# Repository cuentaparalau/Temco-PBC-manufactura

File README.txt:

-----------TEMCO Grupo 9-----------
Juan Arzola
Alexis Rabiller
Manuel Simon
-----------------------------------

Para los part number se usaron los entregados por los fabricantes
Se verifico la disponibilidad de las componentes con su respectivo part-number en DigiKey
En el .zip se encuentran los archivos de manufactura

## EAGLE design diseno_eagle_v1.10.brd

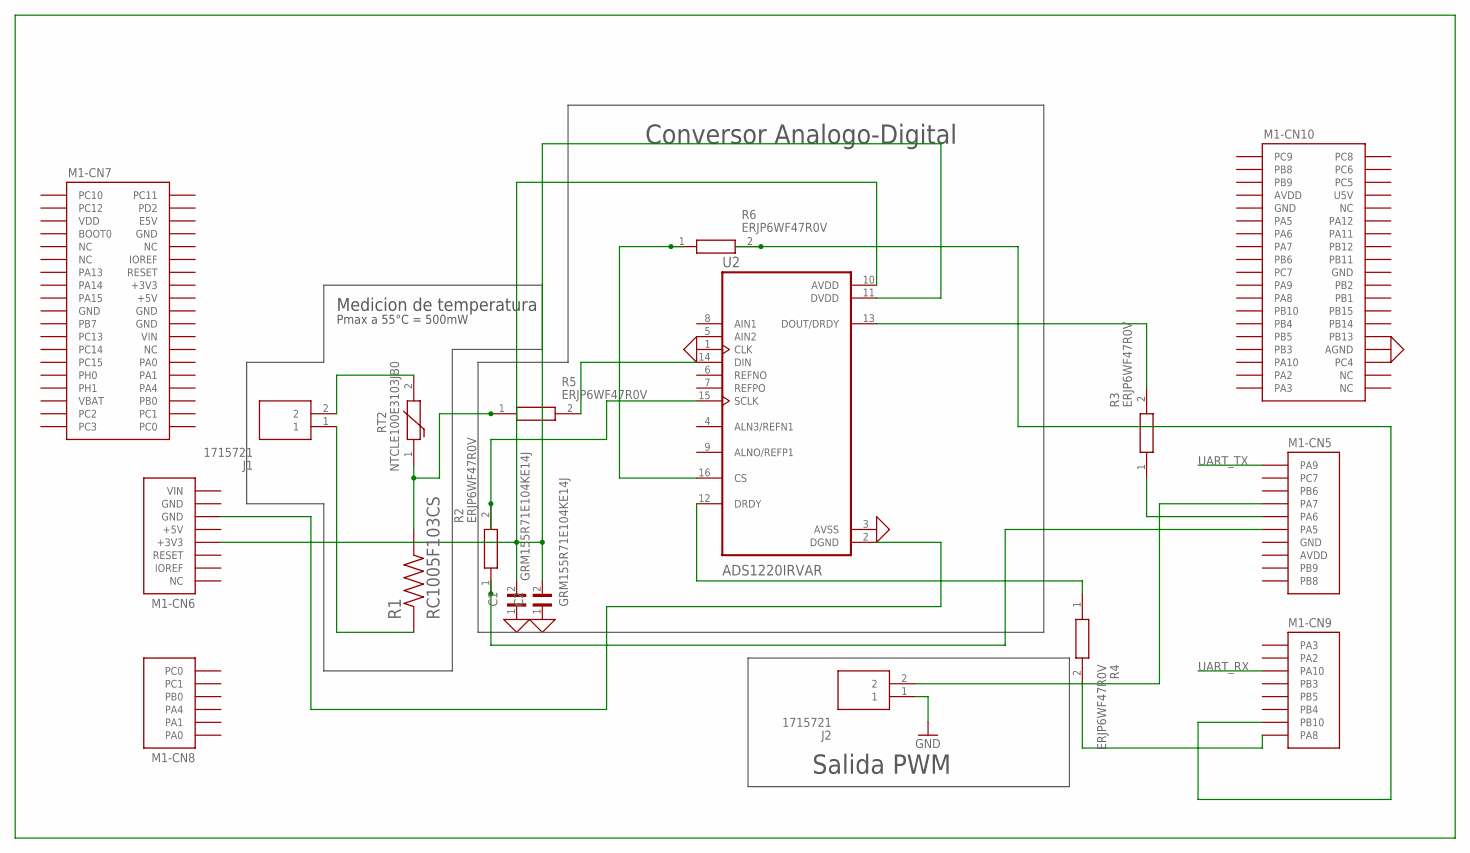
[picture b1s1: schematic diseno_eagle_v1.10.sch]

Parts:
C1, C2: GRM155R71E104KE14J; CAPC1005X55N
J1, J2: 1715721
M1: NUCLEO-L452RE; NUCLEO-64
R1: RC1005F103CS; RESC1005X40N
R2, R3, R4, R5, R6: ERJP6WF47R0V; RESC2012X75N
RT2: NTCLE100E3103JB0
U2: ADS1220IRVAR; QFN50P350X350X100-17N

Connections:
0: C1.1, C2.1, M1.CN10-32 (AGND), U2.1 (CLK), U2.3 (AVSS)
+3V3: M1.CN7-16 (+3V3)
+5V: M1.CN6-5 (+5V), M1.CN7-18 (+5V)
AVDD: M1.CN5-8 (AVDD), M1.CN10-7 (AVDD)
GND: J2.1, M1.CN5-7 (GND), M1.CN6-7 (GND), M1.CN7-8 (GND), M1.CN7-19 (GND), M1.CN7-20 (GND), M1.CN7-22 (GND), M1.CN10-9 (GND), M1.CN10-20 (GND)
IOREF: M1.CN6-2 (IOREF)
unnamed: R4.1, U2.12 (DRDY)
unnamed: R3.2, U2.13 (DOUT/DRDY)
unnamed: R1.2, R5.1, RT2.1
unnamed: M1.CN5-6 (PA5), R2.1
unnamed: M1.CN9-7 (PB10), R6.2
unnamed: M1.CN5-5 (PA6), R3.1
unnamed: C1.2, C2.2, M1.CN6-4 (+3V3), U2.10 (AVDD), U2.11 (DVDD)
unnamed: M1.CN6-6 (GND), U2.2 (DGND)
unnamed: M1.CN9-8 (PA8), R4.2
unnamed: J1.2, RT2.2
unnamed: R5.2, U2.14 (DIN)
unnamed: J1.1, R1.1
unnamed: J2.2, M1.CN5-4 (PA7)
unnamed: R6.1, U2.16 (CS)
unnamed: R2.2, U2.15 (SCLK)
U5V: M1.CN10-8 (U5V)
UART_RX: M1.CN9-3 (PA10)
UART_TX: M1.CN5-1 (PA9)
VBAT: M1.CN7-33 (VBAT)
VDD: M1.CN7-5 (VDD)
VIN: M1.CN6-8 (VIN), M1.CN7-24 (VIN)

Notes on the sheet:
Salida PWM
Medicion de temperatura
Conversor Analogo-Digital
Pmax a 55°C = 500mW

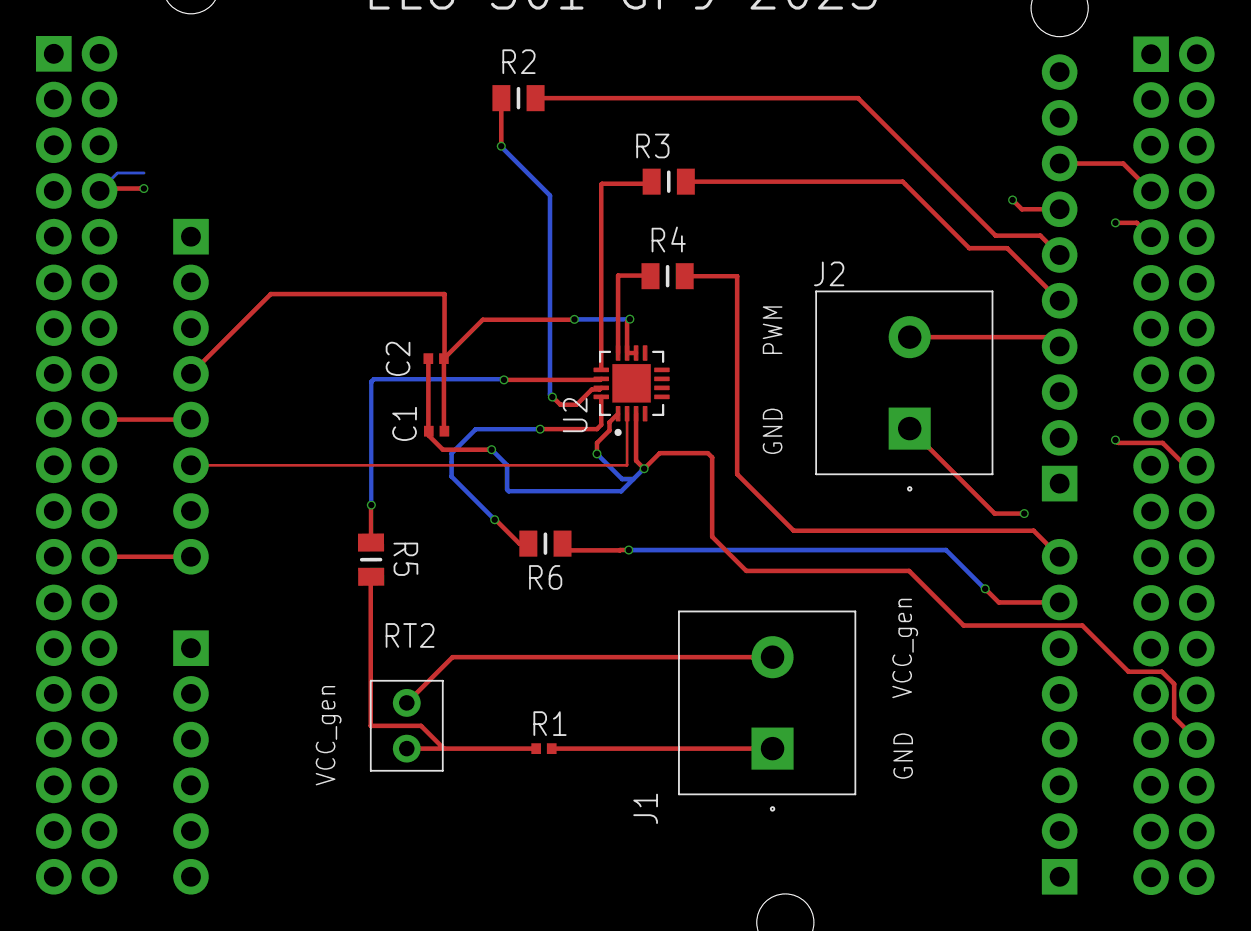
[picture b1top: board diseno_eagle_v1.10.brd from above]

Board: 2 copper layers, 13 parts (0 on the bottom side), 20 nets.
